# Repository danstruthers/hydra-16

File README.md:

## **Hydra 16**

A multitasking 65C02 computer and its operating system, HydraOS.

The Hydra-16's hardware gives each of 16 tasks its own 32K of RAM, zero page and stack included, with its own RAM and ROM bank selections, so a task switch is one register write.  HydraOS runs on it, Plan 9's way:
* **One kernel** in the BIOS ROM: a preemptive scheduler, one interrupt path, notes, memory and banks, and a jump table made from a specification.  Everything else is a module of the paged ROM, run in place in a task of its own.
* **A base to build on:** the kernel, a serial console driver, the kernel's devices and Woz's monitor are the base (`base/`), which HydraOS is built on and which boots on its own: [write an OS of your own](docs/09-programming/your-own-os.md) on it.
* **Everything a file:** devices are file servers (the console's windows, the disks and HydraFS, sound, GPIO and I2C, the clock, the Vera X, and `/pc`, a folder on the PC over the serial line), and each task has a namespace of its own, built by binds and mounts.
* **Shells and languages:** rc, Plan 9's shell, and the core tools; HyForth (Forth 2012), the login shell; hylang (danlang, a lisp); HyBASIC (QuickBASIC's kind, every number exact); SDKs for C (cc65) and assembly, and `as`, an assembler on the Hydra itself.
* **Tools:** a screen editor (`edit`), a debugger (`db`), a song player that plays ZSM songs and compiles scores as it plays.

The code is built with **cc65** (https://cc65.github.io/), and the board is designed in **KiCad 9** (https://www.kicad.org).

### **Quick start**

```
cd base
node build.js                      the base alone: the kernel, ser, kdev, the monitor (bin/bios_*.bin, bin/prom0.bin)
node sim/run.js -i                 its monitor in your terminal (Ctrl-A x quits)

cd ../reborn
node build.js                      build HydraOS (needs Node.js and cc65): bin/bios_*.bin, bin/prom0.bin ...
node sim/run.js -i                 use the Hydra in your terminal, in the emulator (Ctrl-A x quits)
node sim/web.js                    the emulator in a browser: one file, bin/hydra-16.html, to open (in Git: no
                                   Node.js needed to use it)
node sim/test.js                   the regression tests
```

The ROM images are in Git (`reborn/bin/`) and on each GitHub release, so the chips can be programmed without a toolchain.

### **Documentation**

**[The Hydra-16 book](docs/README.md)** is everything, in order: what the machine is, the board and how to build it
(the parts, the layout, the quirks), the kernel and its calls, the drivers, the shell, the languages, the tools, the
emulator, and the programming guide.  It's also [one PDF](docs/hydra-16.pdf), to print.

| Chapter | |
| :------ | :- |
| [1. The Hydra-16 at a glance](docs/01-overview.md) | The ideas, the software in layers, and a first hour in the emulator |
| [2. The hardware](docs/02-hardware/README.md) | The architecture, the devices, the parts, building it, the layout, the quirks, the cards |
| [3. The base](docs/03-base/README.md) | The boot, the kernel, files and namespaces, the system calls, the monitor |
| [4. The drivers](docs/04-drivers/README.md) | The serial console, the kernel's devices, storage, sound, GPIO, video |
| [5. The shell: rc](docs/05-rc.md) | Plan 9's shell |
| [6. The languages](docs/06-languages/README.md) | HyForth, hylang, HyBASIC, and the numbers they share |
| [7. The tools](docs/07-tools.md) | The core tools, the editors, the debugger, the assembler and disassembler |
| [8. The emulator](docs/08-emulator.md) | The emulator, the build, the tests, the PC tools |
| [9. The programming guide](docs/09-programming/README.md) | Assembly, C, servers and drivers, libraries, your own OS, every system call |

How it was designed, and where it stands: [the plan and the design notes](docs/design/README.md).

### **Repository**

| Folder | What |
| :----- | :--- |
| `base/` | The base: the kernel (the BIOS ROM), the system calls' specification, the console driver `ser`, the kernel's devices `kdev`, the monitor `wozmon`, the assembly SDK's core, the board's emulator and the tests' runner |
| `reborn/` | HydraOS, on the base: its modules, the SDKs, the ROM disk, the SD card's image, its tests |
| `docs/` | The book (its chapters, `docs/build`: the tools that make its parts list, layout drawings, call reference and PDF), and the design notes (`docs/design`) |
| `board/` | KiCad schematics and PCBs: the main board, the memory daughter card, the bus breakout card, the Vera X's glue board |
| `old/` | The old system (the 1.8C line: `os_rom/`, its programs, emulator, build and documents), frozen at HydraOS 1.0; `node old/build.js test` still builds and tests it |

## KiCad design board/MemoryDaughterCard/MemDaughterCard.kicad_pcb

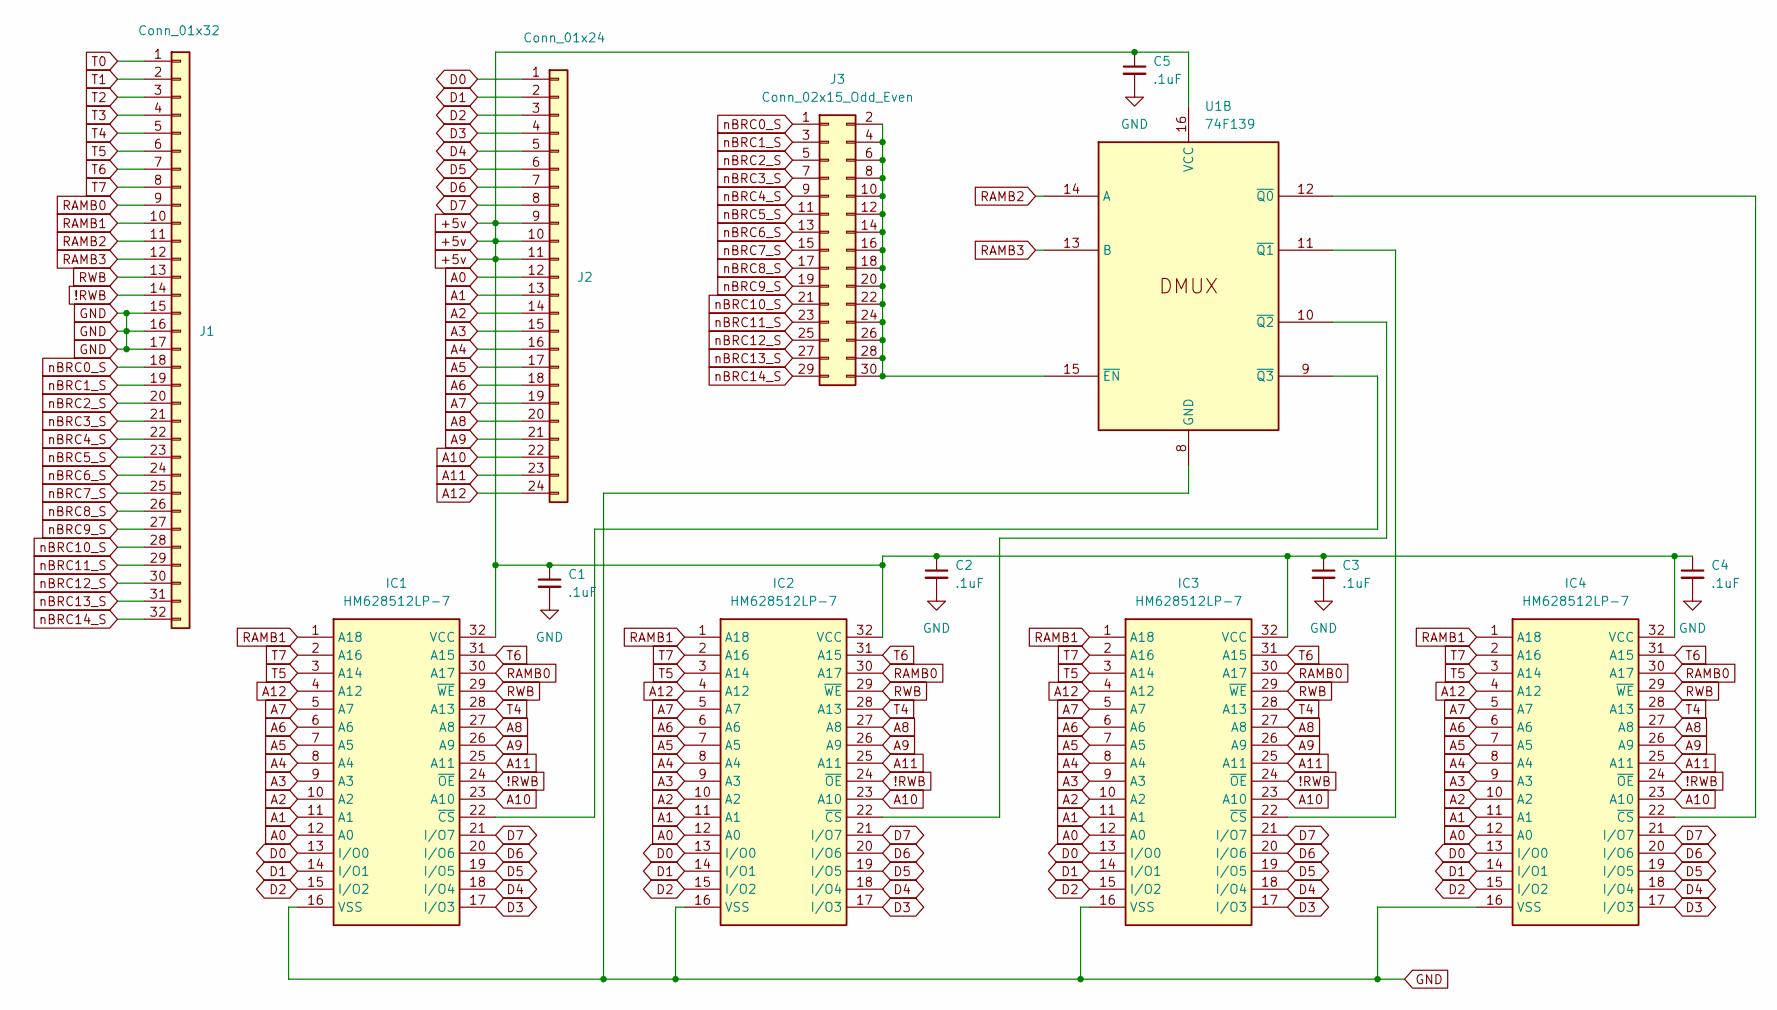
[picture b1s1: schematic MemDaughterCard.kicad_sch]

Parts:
C1, C2, C3, C4, C5: .1uF; C_Disc_D5.0mm_W2.5mm_P5.00mm
IC1, IC2, IC3, IC4: HM628512LP-7; DIP-32_W15.24mm_Socket_LongPads; Manufacturer_Part_Number HM628512LFP-7
J1: Conn_01x32; PinHeader_1x32_P2.54mm_Vertical
J2: Conn_01x24; PinHeader_1x24_P2.54mm_Vertical
J3: Conn_02x15_Odd_Even; PinHeader_2x15_P2.54mm_Vertical
U1: 74F139; DIP-16_W7.62mm

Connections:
!RWB: IC1.24 (~OE), IC2.24 (~OE), IC3.24 (~OE), IC4.24 (~OE), J1.14
+5v: C1.1, C2.1, C3.1, C4.1, C5.1, IC1.32 (VCC), IC2.32 (VCC), IC3.32 (VCC), IC4.32 (VCC), J2.9, J2.10, J2.11, U1.16 (VCC)
A0: IC1.12 (A0), IC2.12 (A0), IC3.12 (A0), IC4.12 (A0), J2.12
A1: IC1.11 (A1), IC2.11 (A1), IC3.11 (A1), IC4.11 (A1), J2.13
A2: IC1.10 (A2), IC2.10 (A2), IC3.10 (A2), IC4.10 (A2), J2.14
A3: IC1.9 (A3), IC2.9 (A3), IC3.9 (A3), IC4.9 (A3), J2.15
A4: IC1.8 (A4), IC2.8 (A4), IC3.8 (A4), IC4.8 (A4), J2.16
A5: IC1.7 (A5), IC2.7 (A5), IC3.7 (A5), IC4.7 (A5), J2.17
A6: IC1.6 (A6), IC2.6 (A6), IC3.6 (A6), IC4.6 (A6), J2.18
A7: IC1.5 (A7), IC2.5 (A7), IC3.5 (A7), IC4.5 (A7), J2.19
A8: IC1.27 (A8), IC2.27 (A8), IC3.27 (A8), IC4.27 (A8), J2.20
A9: IC1.26 (A9), IC2.26 (A9), IC3.26 (A9), IC4.26 (A9), J2.21
A10: IC1.23 (A10), IC2.23 (A10), IC3.23 (A10), IC4.23 (A10), J2.22
A11: IC1.25 (A11), IC2.25 (A11), IC3.25 (A11), IC4.25 (A11), J2.23
A12: IC1.4 (A12), IC2.4 (A12), IC3.4 (A12), IC4.4 (A12), J2.24
D0: IC1.13 (I/O0), IC2.13 (I/O0), IC3.13 (I/O0), IC4.13 (I/O0), J2.1
D1: IC1.14 (I/O1), IC2.14 (I/O1), IC3.14 (I/O1), IC4.14 (I/O1), J2.2
D2: IC1.15 (I/O2), IC2.15 (I/O2), IC3.15 (I/O2), IC4.15 (I/O2), J2.3
D3: IC1.17 (I/O3), IC2.17 (I/O3), IC3.17 (I/O3), IC4.17 (I/O3), J2.4
D4: IC1.18 (I/O4), IC2.18 (I/O4), IC3.18 (I/O4), IC4.18 (I/O4), J2.5
D5: IC1.19 (I/O5), IC2.19 (I/O5), IC3.19 (I/O5), IC4.19 (I/O5), J2.6
D6: IC1.20 (I/O6), IC2.20 (I/O6), IC3.20 (I/O6), IC4.20 (I/O6), J2.7
D7: IC1.21 (I/O7), IC2.21 (I/O7), IC3.21 (I/O7), IC4.21 (I/O7), J2.8
GND: C1.2, C2.2, C3.2, C4.2, C5.2, IC1.16 (VSS), IC2.16 (VSS), IC3.16 (VSS), IC4.16 (VSS), J1.15, J1.16, J1.17, U1.8 (GND)
unnamed: IC1.22 (~CS), U1.9 (~Q3)
unnamed: IC2.22 (~CS), U1.10 (~Q2)
unnamed: IC3.22 (~CS), U1.11 (~Q1)
unnamed: IC4.22 (~CS), U1.12 (~Q0)
unnamed: J3.2, J3.4, J3.6, J3.8, J3.10, J3.12, J3.14, J3.16, J3.18, J3.20, J3.22, J3.24, J3.26, J3.28, J3.30, U1.15 (~EN)
RAMB0: IC1.30 (A17), IC2.30 (A17), IC3.30 (A17), IC4.30 (A17), J1.9
RAMB1: IC1.1 (A18), IC2.1 (A18), IC3.1 (A18), IC4.1 (A18), J1.10
RAMB2: J1.11, U1.14 (A)
RAMB3: J1.12, U1.13 (B)
RWB: IC1.29 (~WE), IC2.29 (~WE), IC3.29 (~WE), IC4.29 (~WE), J1.13
T0: J1.1
T1: J1.2
T2: J1.3
T3: J1.4
T4: IC1.28 (A13), IC2.28 (A13), IC3.28 (A13), IC4.28 (A13), J1.5
T5: IC1.3 (A14), IC2.3 (A14), IC3.3 (A14), IC4.3 (A14), J1.6
T6: IC1.31 (A15), IC2.31 (A15), IC3.31 (A15), IC4.31 (A15), J1.7
T7: IC1.2 (A16), IC2.2 (A16), IC3.2 (A16), IC4.2 (A16), J1.8
nBRC0_S: J1.18, J3.1
nBRC1_S: J1.19, J3.3
nBRC2_S: J1.20, J3.5
nBRC3_S: J1.21, J3.7
nBRC4_S: J1.22, J3.9
nBRC5_S: J1.23, J3.11
nBRC6_S: J1.24, J3.13
nBRC7_S: J1.25, J3.15
nBRC8_S: J1.26, J3.17
nBRC9_S: J1.27, J3.19
nBRC10_S: J1.28, J3.21
nBRC11_S: J1.29, J3.23
nBRC12_S: J1.30, J3.25
nBRC13_S: J1.31, J3.27
nBRC14_S: J1.32, J3.29

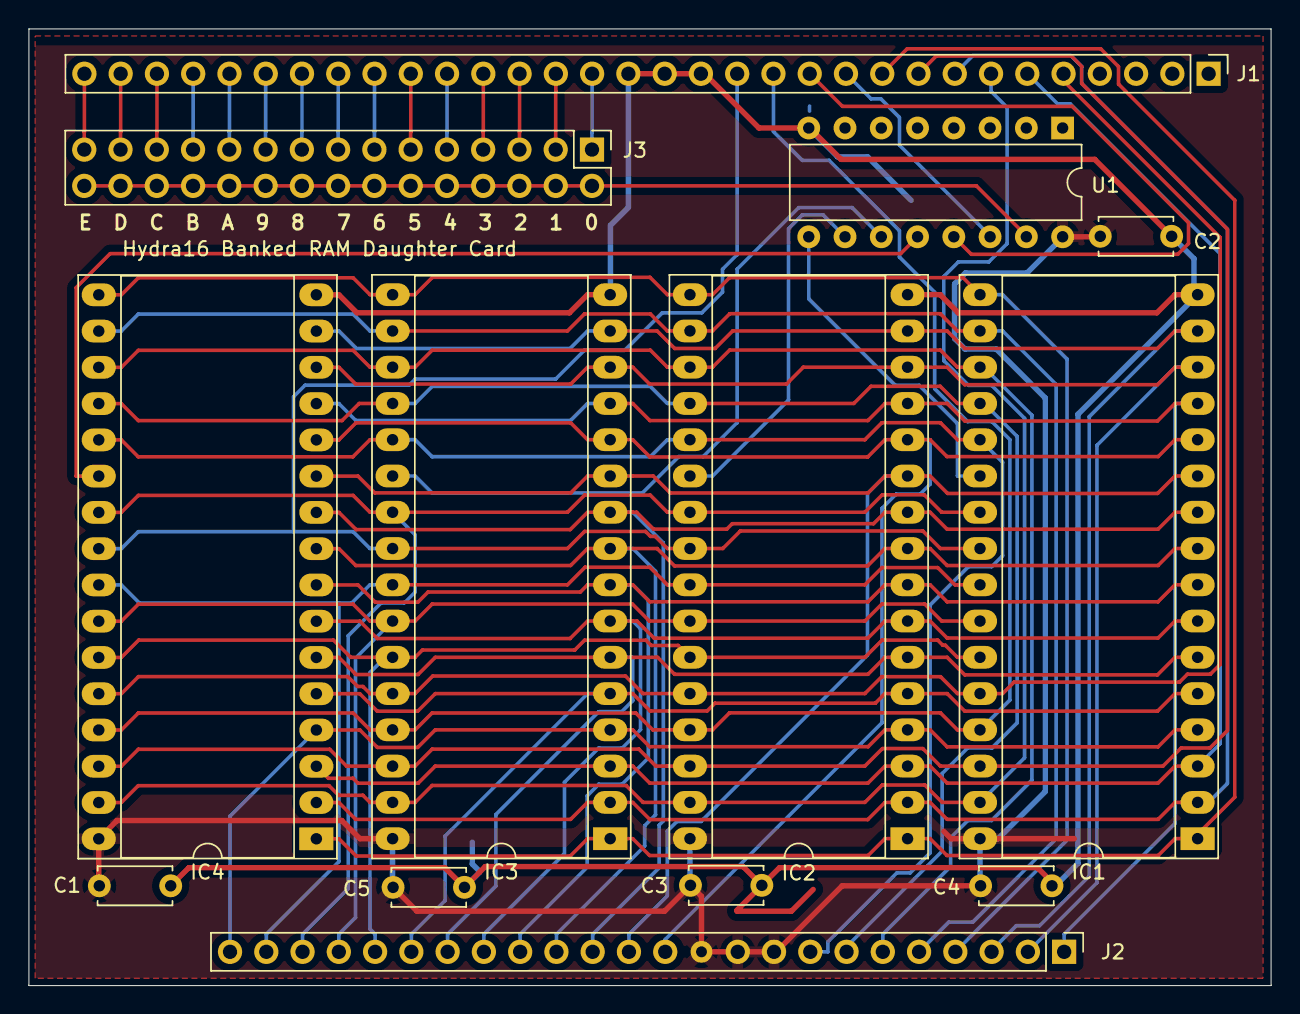
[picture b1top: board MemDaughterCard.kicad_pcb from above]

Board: 2 copper layers, 87.0 x 67.0 mm, 13 parts (0 on the bottom side), 53 nets.

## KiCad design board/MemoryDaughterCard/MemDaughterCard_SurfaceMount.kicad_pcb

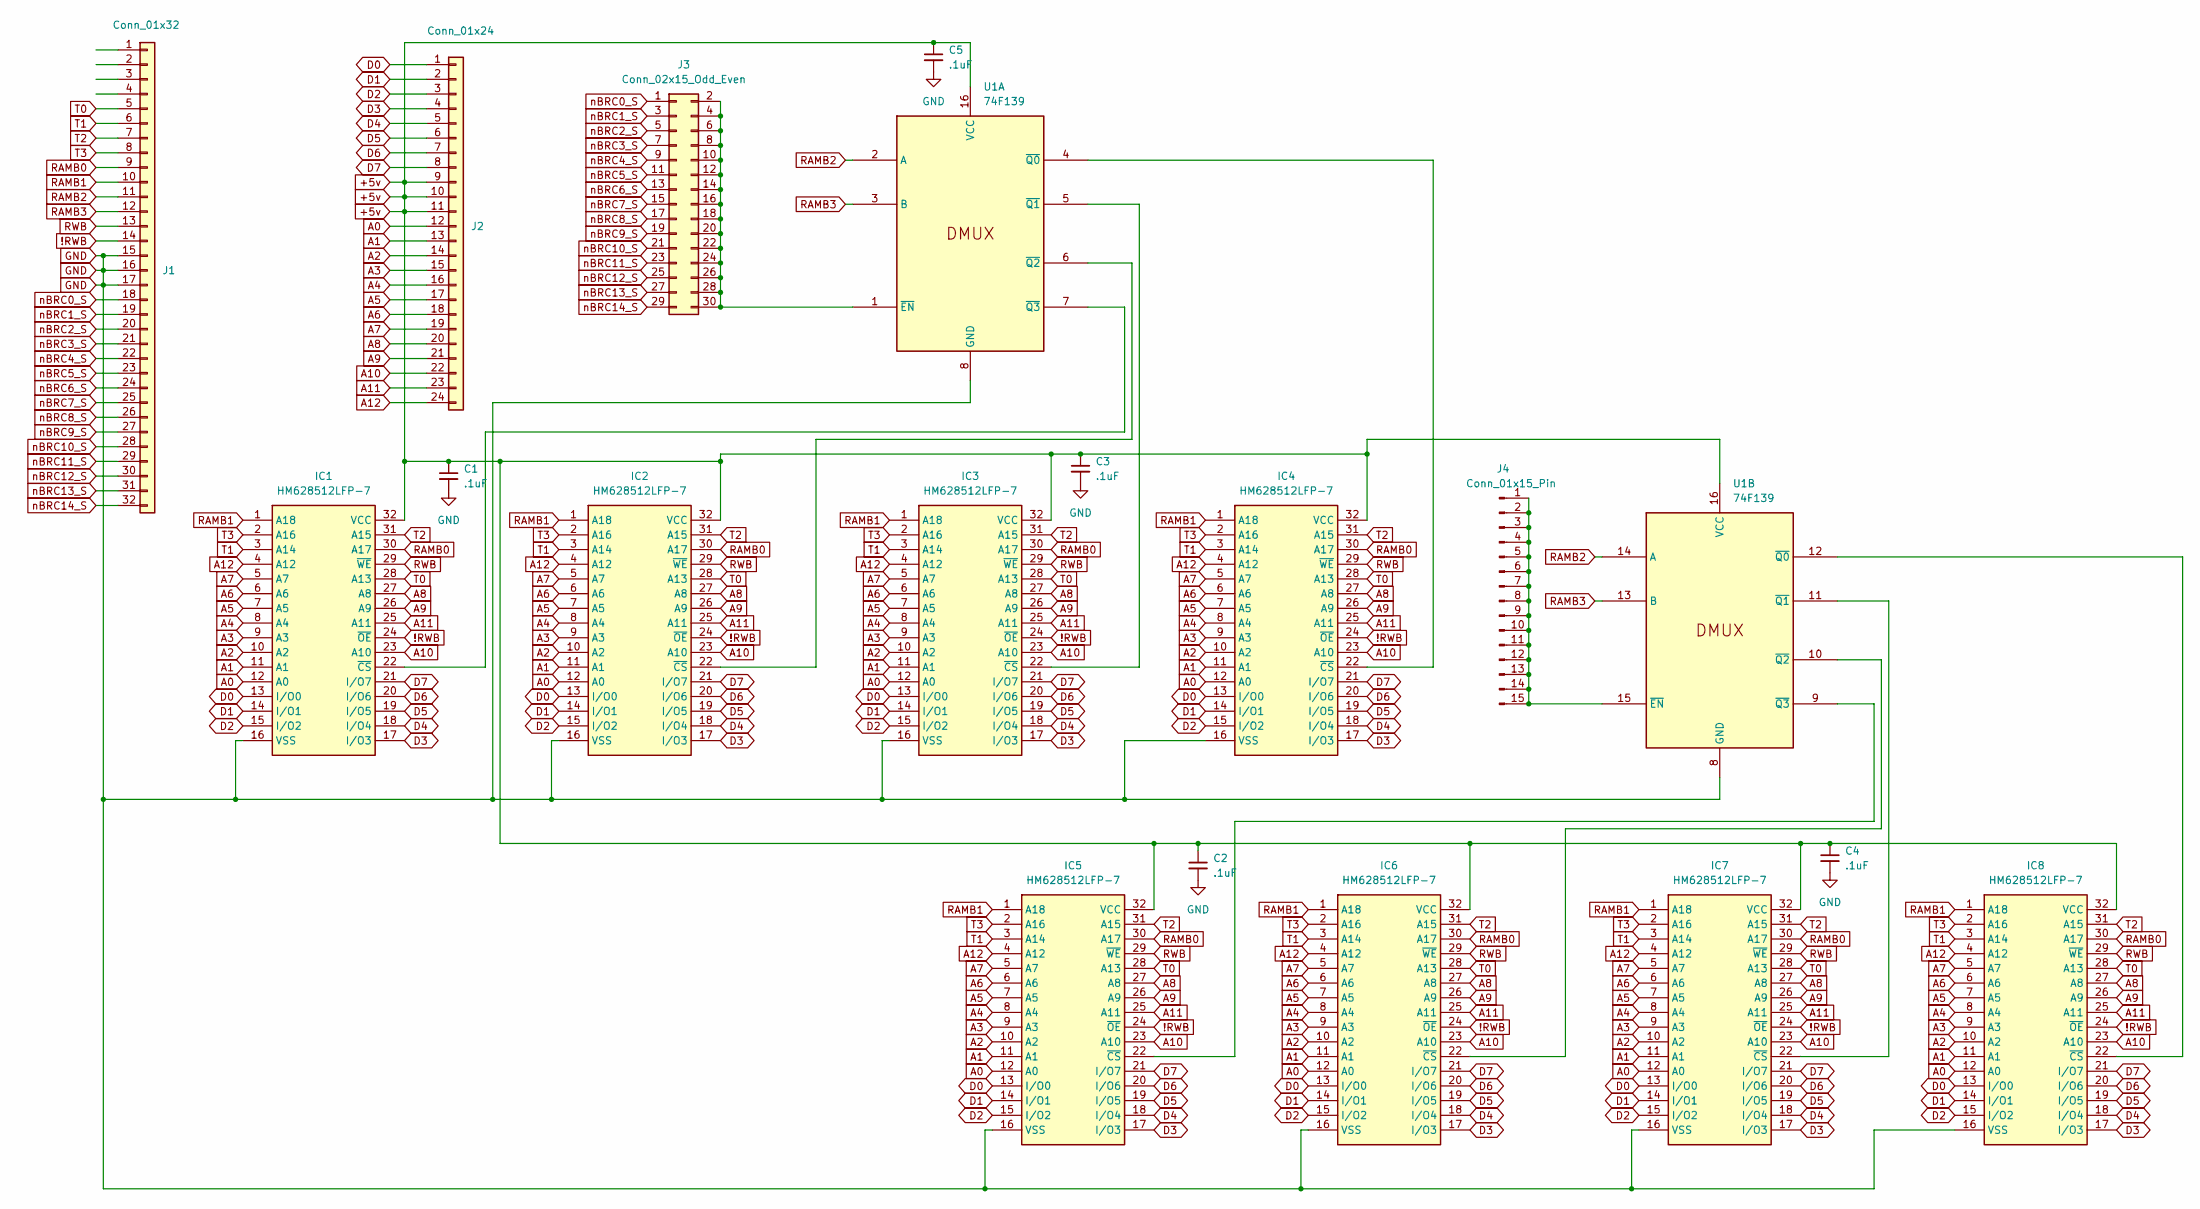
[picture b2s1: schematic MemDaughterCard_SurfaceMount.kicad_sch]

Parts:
C1, C2, C3, C4, C5: .1uF; C_Disc_D5.0mm_W2.5mm_P5.00mm
IC1, IC2, IC3, IC4, IC5, IC6, IC7, IC8: HM628512LFP-7; SOIC127P1414X300-32N; Manufacturer_Part_Number HM628512LFP-7
J1: Conn_01x32; PinHeader_1x32_P2.54mm_Vertical
J2: Conn_01x24; PinHeader_1x24_P2.54mm_Vertical
J3: Conn_02x15_Odd_Even; PinHeader_2x15_P2.54mm_Vertical
J4: Conn_01x15_Pin; PinHeader_1x15_P2.54mm_Vertical
U1: 74F139; DIP-16_W7.62mm

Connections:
!RWB: IC1.24 (~OE), IC2.24 (~OE), IC3.24 (~OE), IC4.24 (~OE), IC5.24 (~OE), IC6.24 (~OE), IC7.24 (~OE), IC8.24 (~OE), J1.14
+5v: C1.1, C2.1, C3.1, C4.1, C5.1, IC1.32 (VCC), IC2.32 (VCC), IC3.32 (VCC), IC4.32 (VCC), IC5.32 (VCC), IC6.32 (VCC), IC7.32 (VCC), IC8.32 (VCC), J2.9, J2.10, J2.11, U1.16 (VCC)
A0: IC1.12 (A0), IC2.12 (A0), IC3.12 (A0), IC4.12 (A0), IC5.12 (A0), IC6.12 (A0), IC7.12 (A0), IC8.12 (A0), J2.12
A1: IC1.11 (A1), IC2.11 (A1), IC3.11 (A1), IC4.11 (A1), IC5.11 (A1), IC6.11 (A1), IC7.11 (A1), IC8.11 (A1), J2.13
A2: IC1.10 (A2), IC2.10 (A2), IC3.10 (A2), IC4.10 (A2), IC5.10 (A2), IC6.10 (A2), IC7.10 (A2), IC8.10 (A2), J2.14
A3: IC1.9 (A3), IC2.9 (A3), IC3.9 (A3), IC4.9 (A3), IC5.9 (A3), IC6.9 (A3), IC7.9 (A3), IC8.9 (A3), J2.15
A4: IC1.8 (A4), IC2.8 (A4), IC3.8 (A4), IC4.8 (A4), IC5.8 (A4), IC6.8 (A4), IC7.8 (A4), IC8.8 (A4), J2.16
A5: IC1.7 (A5), IC2.7 (A5), IC3.7 (A5), IC4.7 (A5), IC5.7 (A5), IC6.7 (A5), IC7.7 (A5), IC8.7 (A5), J2.17
A6: IC1.6 (A6), IC2.6 (A6), IC3.6 (A6), IC4.6 (A6), IC5.6 (A6), IC6.6 (A6), IC7.6 (A6), IC8.6 (A6), J2.18
A7: IC1.5 (A7), IC2.5 (A7), IC3.5 (A7), IC4.5 (A7), IC5.5 (A7), IC6.5 (A7), IC7.5 (A7), IC8.5 (A7), J2.19
A8: IC1.27 (A8), IC2.27 (A8), IC3.27 (A8), IC4.27 (A8), IC5.27 (A8), IC6.27 (A8), IC7.27 (A8), IC8.27 (A8), J2.20
A9: IC1.26 (A9), IC2.26 (A9), IC3.26 (A9), IC4.26 (A9), IC5.26 (A9), IC6.26 (A9), IC7.26 (A9), IC8.26 (A9), J2.21
A10: IC1.23 (A10), IC2.23 (A10), IC3.23 (A10), IC4.23 (A10), IC5.23 (A10), IC6.23 (A10), IC7.23 (A10), IC8.23 (A10), J2.22
A11: IC1.25 (A11), IC2.25 (A11), IC3.25 (A11), IC4.25 (A11), IC5.25 (A11), IC6.25 (A11), IC7.25 (A11), IC8.25 (A11), J2.23
A12: IC1.4 (A12), IC2.4 (A12), IC3.4 (A12), IC4.4 (A12), IC5.4 (A12), IC6.4 (A12), IC7.4 (A12), IC8.4 (A12), J2.24
D0: IC1.13 (I/O0), IC2.13 (I/O0), IC3.13 (I/O0), IC4.13 (I/O0), IC5.13 (I/O0), IC6.13 (I/O0), IC7.13 (I/O0), IC8.13 (I/O0), J2.1
D1: IC1.14 (I/O1), IC2.14 (I/O1), IC3.14 (I/O1), IC4.14 (I/O1), IC5.14 (I/O1), IC6.14 (I/O1), IC7.14 (I/O1), IC8.14 (I/O1), J2.2
D2: IC1.15 (I/O2), IC2.15 (I/O2), IC3.15 (I/O2), IC4.15 (I/O2), IC5.15 (I/O2), IC6.15 (I/O2), IC7.15 (I/O2), IC8.15 (I/O2), J2.3
D3: IC1.17 (I/O3), IC2.17 (I/O3), IC3.17 (I/O3), IC4.17 (I/O3), IC5.17 (I/O3), IC6.17 (I/O3), IC7.17 (I/O3), IC8.17 (I/O3), J2.4
D4: IC1.18 (I/O4), IC2.18 (I/O4), IC3.18 (I/O4), IC4.18 (I/O4), IC5.18 (I/O4), IC6.18 (I/O4), IC7.18 (I/O4), IC8.18 (I/O4), J2.5
D5: IC1.19 (I/O5), IC2.19 (I/O5), IC3.19 (I/O5), IC4.19 (I/O5), IC5.19 (I/O5), IC6.19 (I/O5), IC7.19 (I/O5), IC8.19 (I/O5), J2.6
D6: IC1.20 (I/O6), IC2.20 (I/O6), IC3.20 (I/O6), IC4.20 (I/O6), IC5.20 (I/O6), IC6.20 (I/O6), IC7.20 (I/O6), IC8.20 (I/O6), J2.7
D7: IC1.21 (I/O7), IC2.21 (I/O7), IC3.21 (I/O7), IC4.21 (I/O7), IC5.21 (I/O7), IC6.21 (I/O7), IC7.21 (I/O7), IC8.21 (I/O7), J2.8
GND: C1.2, C2.2, C3.2, C4.2, C5.2, IC1.16 (VSS), IC2.16 (VSS), IC3.16 (VSS), IC4.16 (VSS), IC5.16 (VSS), IC6.16 (VSS), IC7.16 (VSS), IC8.16 (VSS), J1.15, J1.16, J1.17, U1.8 (GND)
unnamed: IC1.22 (~CS), U1.7 (~Q3)
unnamed: IC2.22 (~CS), U1.6 (~Q2)
unnamed: IC3.22 (~CS), U1.5 (~Q1)
unnamed: IC4.22 (~CS), U1.4 (~Q0)
unnamed: IC5.22 (~CS), U1.9 (~Q3)
unnamed: IC6.22 (~CS), U1.10 (~Q2)
unnamed: IC7.22 (~CS), U1.11 (~Q1)
unnamed: IC8.22 (~CS), U1.12 (~Q0)
unnamed: J3.2, J3.4, J3.6, J3.8, J3.10, J3.12, J3.14, J3.16, J3.18, J3.20, J3.22, J3.24, J3.26, J3.28, J3.30, U1.1 (~EN)
unnamed: J4.1, J4.2, J4.3, J4.4, J4.5, J4.6, J4.7, J4.8, J4.9, J4.10, J4.11, J4.12, J4.13, J4.14, J4.15, U1.15 (~EN)
RAMB0: IC1.30 (A17), IC2.30 (A17), IC3.30 (A17), IC4.30 (A17), IC5.30 (A17), IC6.30 (A17), IC7.30 (A17), IC8.30 (A17), J1.9
RAMB1: IC1.1 (A18), IC2.1 (A18), IC3.1 (A18), IC4.1 (A18), IC5.1 (A18), IC6.1 (A18), IC7.1 (A18), IC8.1 (A18), J1.10
RAMB2: J1.11, U1.2 (A), U1.14 (A)
RAMB3: J1.12, U1.3 (B), U1.13 (B)
RWB: IC1.29 (~WE), IC2.29 (~WE), IC3.29 (~WE), IC4.29 (~WE), IC5.29 (~WE), IC6.29 (~WE), IC7.29 (~WE), IC8.29 (~WE), J1.13
T0: IC1.28 (A13), IC2.28 (A13), IC3.28 (A13), IC4.28 (A13), IC5.28 (A13), IC6.28 (A13), IC7.28 (A13), IC8.28 (A13), J1.5
T1: IC1.3 (A14), IC2.3 (A14), IC3.3 (A14), IC4.3 (A14), IC5.3 (A14), IC6.3 (A14), IC7.3 (A14), IC8.3 (A14), J1.6
T2: IC1.31 (A15), IC2.31 (A15), IC3.31 (A15), IC4.31 (A15), IC5.31 (A15), IC6.31 (A15), IC7.31 (A15), IC8.31 (A15), J1.7
T3: IC1.2 (A16), IC2.2 (A16), IC3.2 (A16), IC4.2 (A16), IC5.2 (A16), IC6.2 (A16), IC7.2 (A16), IC8.2 (A16), J1.8
nBRC0_S: J1.18, J3.1
nBRC1_S: J1.19, J3.3
nBRC2_S: J1.20, J3.5
nBRC3_S: J1.21, J3.7
nBRC4_S: J1.22, J3.9
nBRC5_S: J1.23, J3.11
nBRC6_S: J1.24, J3.13
nBRC7_S: J1.25, J3.15
nBRC8_S: J1.26, J3.17
nBRC9_S: J1.27, J3.19
nBRC10_S: J1.28, J3.21
nBRC11_S: J1.29, J3.23
nBRC12_S: J1.30, J3.25
nBRC13_S: J1.31, J3.27
nBRC14_S: J1.32, J3.29

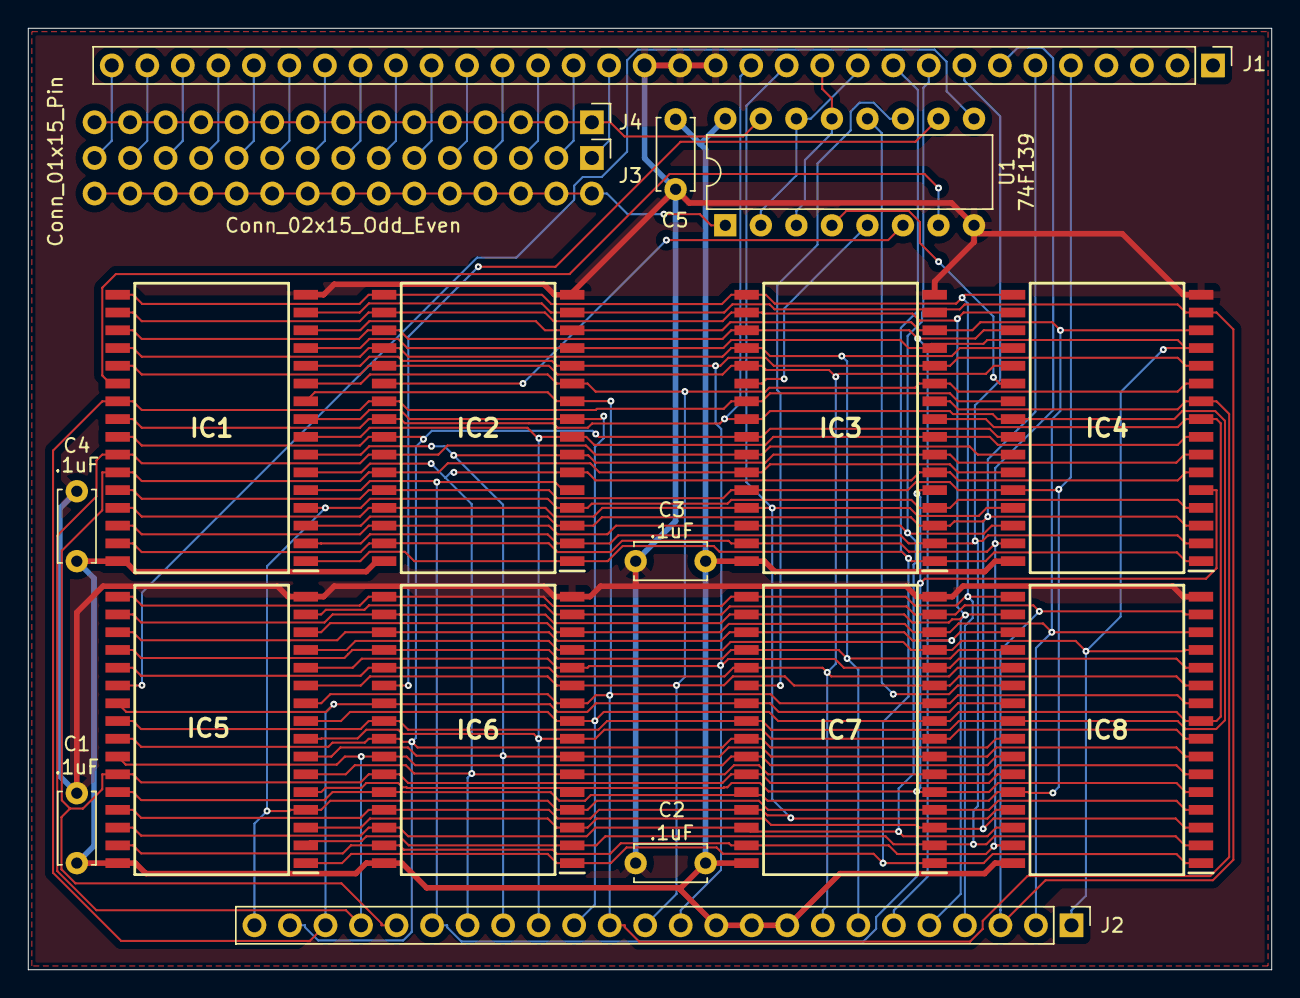
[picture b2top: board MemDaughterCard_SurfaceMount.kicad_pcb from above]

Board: 2 copper layers, 88.9 x 67.3 mm, 18 parts (0 on the bottom side), 58 nets.

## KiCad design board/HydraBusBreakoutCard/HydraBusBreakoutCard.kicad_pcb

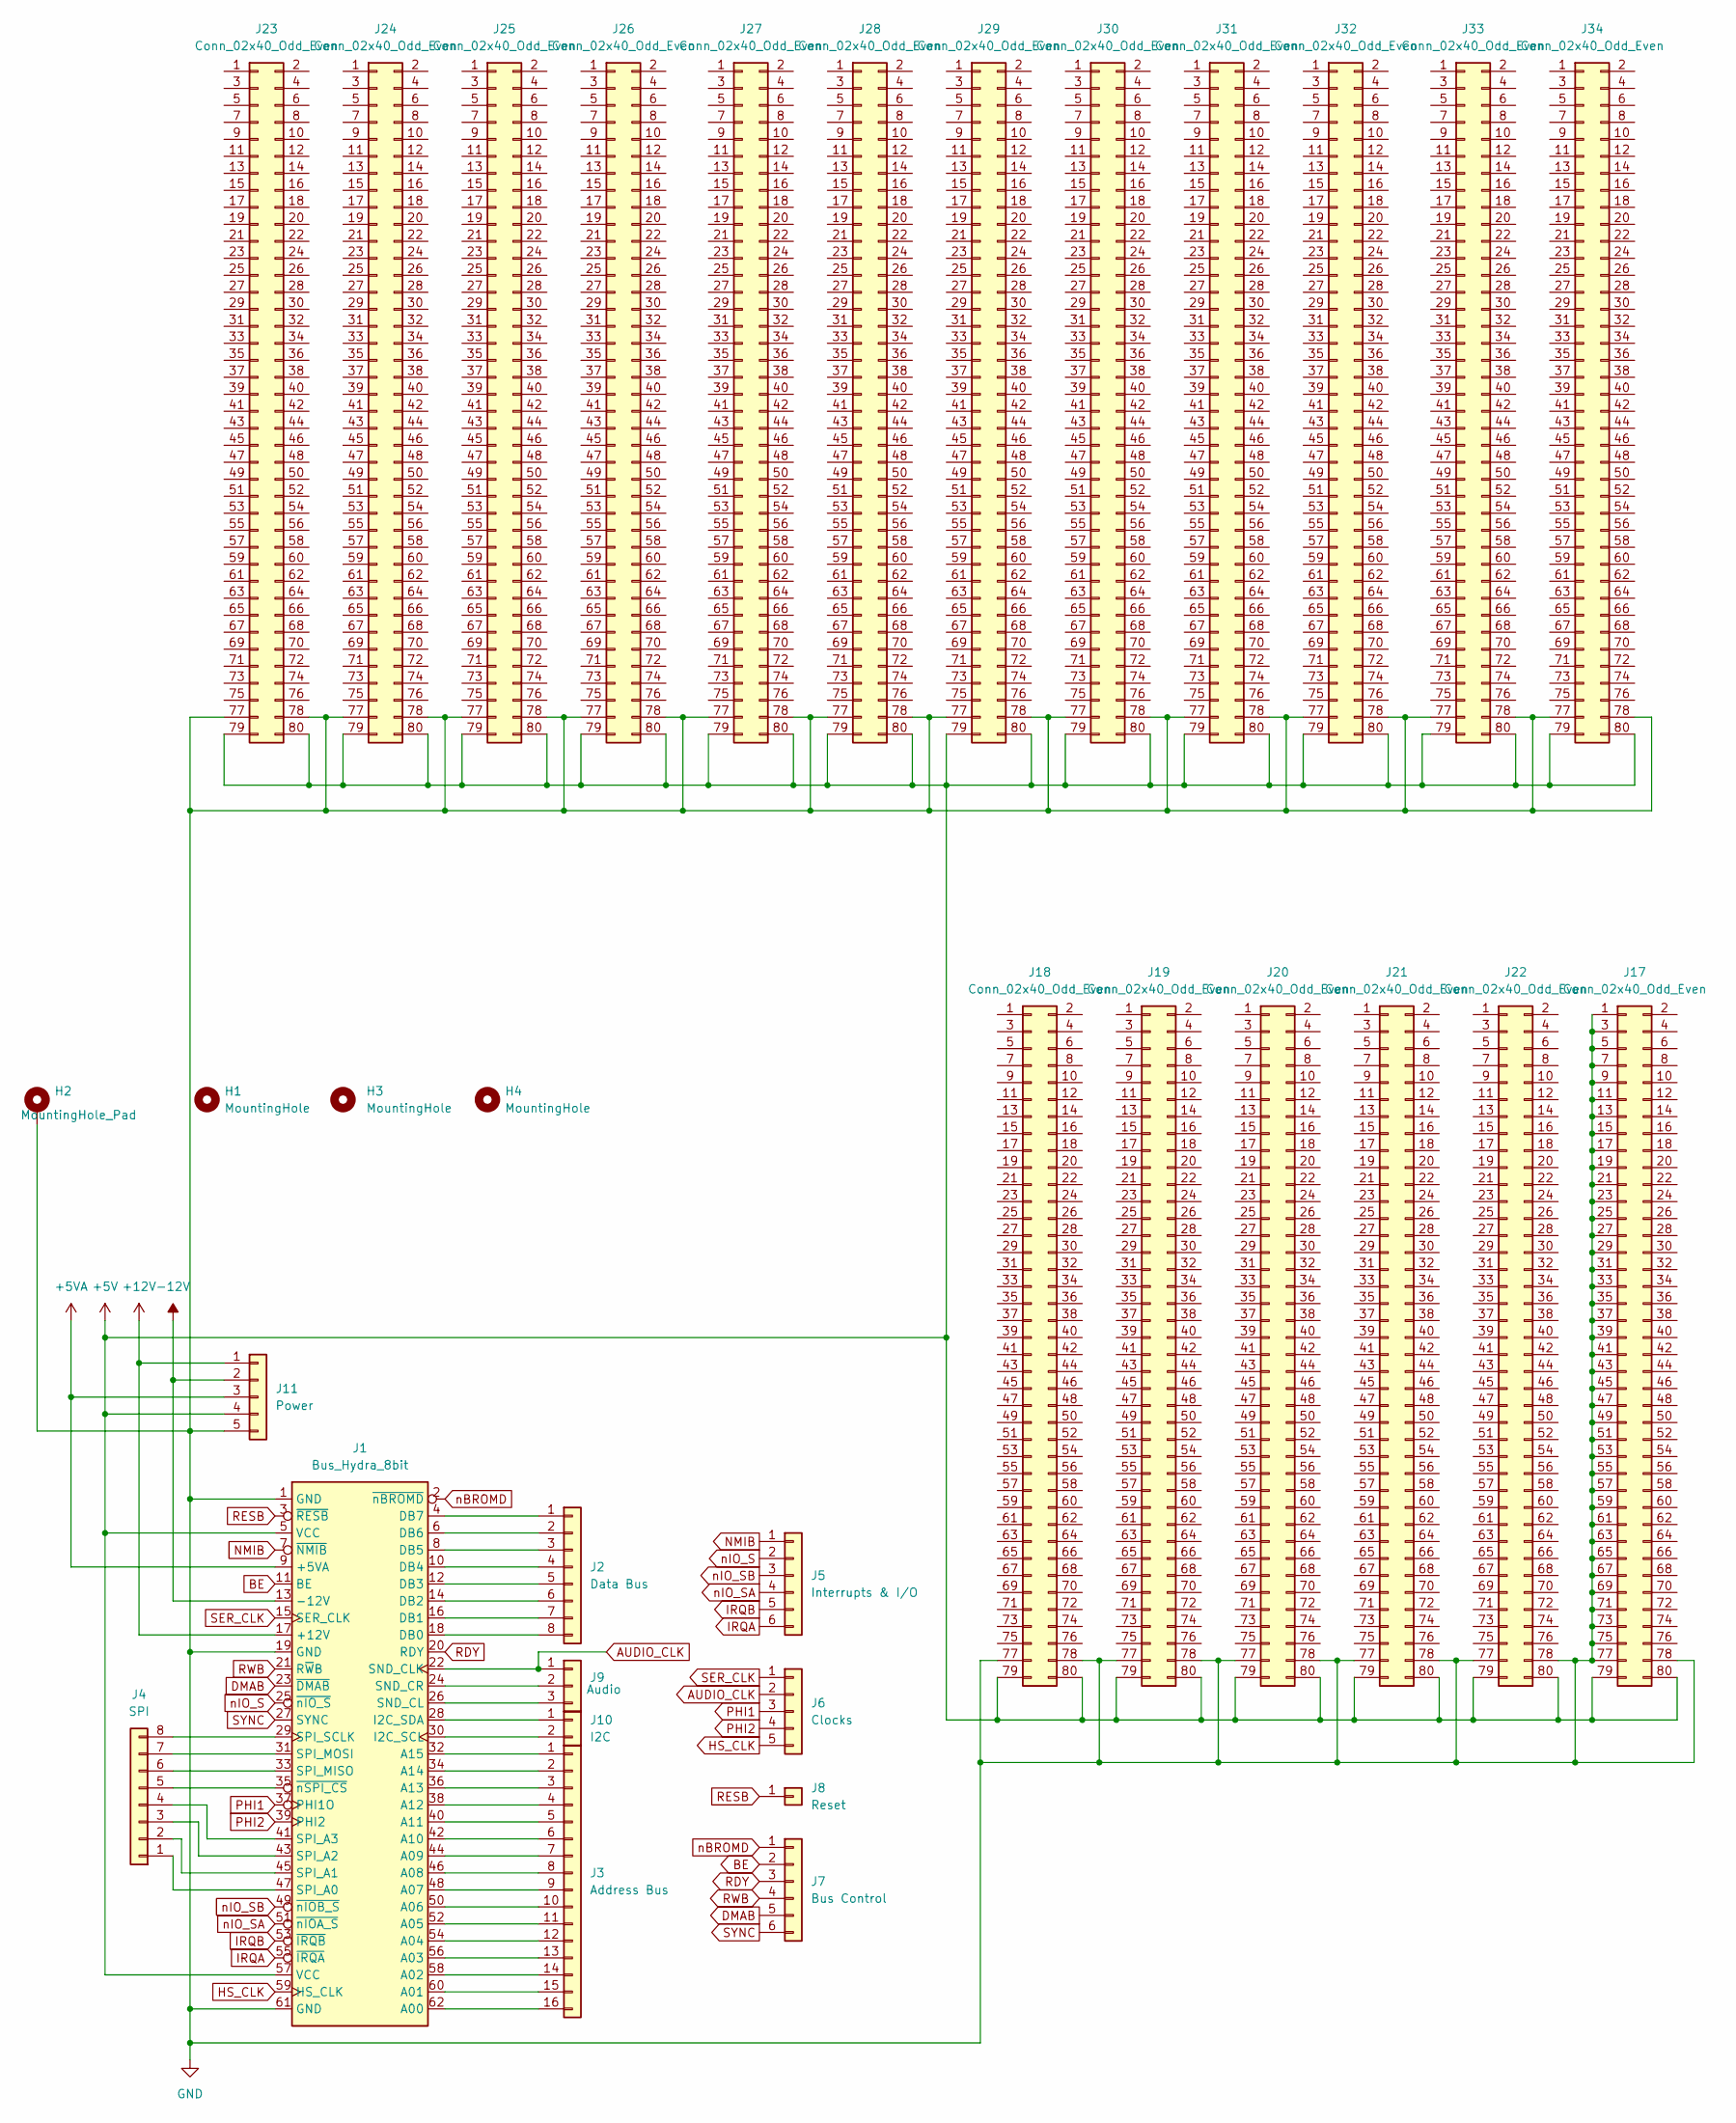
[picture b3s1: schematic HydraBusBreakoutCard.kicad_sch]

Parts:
H1, H3, H4: MountingHole; MountingHole_3.2mm_M3
H2: MountingHole_Pad; MountingHole_3.2mm_M3_ISO7380_Pad_TopBottom
J1: Bus_Hydra_8bit; BUS_Hydra_8Bit
J2: Data Bus; PinHeader_1x08_P2.54mm_Vertical
J3: Address Bus; PinHeader_1x16_P2.54mm_Vertical
J4: SPI; PinHeader_1x08_P2.54mm_Vertical
J5: Interrupts & I/O; PinHeader_1x06_P2.54mm_Vertical
J6: Clocks; PinHeader_1x05_P2.54mm_Vertical
J7: Bus Control; PinHeader_1x06_P2.54mm_Vertical
J8: Reset; PinHeader_1x01_P2.54mm_Vertical
J9: Audio; PinHeader_1x03_P2.54mm_Vertical
J10: I2C; PinHeader_1x02_P2.54mm_Vertical
J11: Power; PinHeader_1x05_P2.54mm_Vertical
J17, J18, J19, J20, J21, J22, J23, J24, J25, J26, J27, J28, J29, J30, J31, J32, J33, J34: Conn_02x40_Odd_Even; PinHeader_2x40_P2.54mm_Vertical

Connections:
+5V: J1.5 (VCC), J1.57 (VCC), J11.4, J17.79, J17.80, J18.79, J18.80, J19.79, J19.80, J20.79, J20.80, J21.79, J21.80, J22.79, J22.80, J23.79, J23.80, J24.79, J24.80, J25.79, J25.80, J26.79, J26.80, J27.79, J27.80, J28.79, J28.80, J29.79, J29.80, J30.79, J30.80, J31.79, J31.80, J32.79, J32.80, J33.79, J33.80, J34.79, J34.80
+5VA: J1.9 (+5VA), J11.3
+12V: J1.17 (+12V), J11.1
-12V: J1.13 (-12V), J11.2
AUDIO_CLK: J1.22 (SND_CLK), J6.2, J9.1
BE: J1.11 (BE), J7.2
DMAB: J1.23 (~DMAB), J7.5
GND: H2.1, J1.1 (GND), J1.19 (GND), J1.61 (GND), J11.5, J17.1, J17.3, J17.5, J17.7, J17.9, J17.11, J17.13, J17.15, J17.17, J17.19, J17.21, J17.23, J17.25, J17.27, J17.29, J17.31, J17.33, J17.35, J17.37, J17.39, J17.41, J17.43, J17.45, J17.47, J17.49, J17.51, J17.53, J17.55, J17.57, J17.59, J17.61, J17.63, J17.65, J17.67, J17.69, J17.71, J17.73, J17.75, J17.77, J17.78, J18.77, J18.78, J19.77, J19.78, J20.77, J20.78, J21.77, J21.78, J22.77, J22.78, J23.77, J23.78, J24.77, J24.78, J25.77, J25.78, J26.77, J26.78, J27.77, J27.78, J28.77, J28.78, J29.77, J29.78, J30.77, J30.78, J31.77, J31.78, J32.77, J32.78, J33.77, J33.78, J34.77, J34.78
HS_CLK: J1.59 (HS_CLK), J6.5
IRQA: J1.55 (~IRQA), J5.6
IRQB: J1.53 (~IRQB), J5.5
NMIB: J1.7 (~NMIB), J5.1
unnamed: J1.62 (A00), J3.16
unnamed: J1.60 (A01), J3.15
unnamed: J1.58 (A02), J3.14
unnamed: J1.56 (A03), J3.13
unnamed: J1.54 (A04), J3.12
unnamed: J1.52 (A05), J3.11
unnamed: J1.50 (A06), J3.10
unnamed: J1.48 (A07), J3.9
unnamed: J1.46 (A08), J3.8
unnamed: J1.44 (A09), J3.7
unnamed: J1.42 (A10), J3.6
unnamed: J1.40 (A11), J3.5
unnamed: J1.38 (A12), J3.4
unnamed: J1.36 (A13), J3.3
unnamed: J1.34 (A14), J3.2
unnamed: J1.32 (A15), J3.1
unnamed: J1.18 (DB0), J2.8
unnamed: J1.16 (DB1), J2.7
unnamed: J1.14 (DB2), J2.6
unnamed: J1.12 (DB3), J2.5
unnamed: J1.10 (DB4), J2.4
unnamed: J1.8 (DB5), J2.3
unnamed: J1.6 (DB6), J2.2
unnamed: J1.4 (DB7), J2.1
unnamed: J1.30 (I2C_SCL), J10.2
unnamed: J1.28 (I2C_SDA), J10.1
unnamed: J1.26 (SND_CL), J9.3
unnamed: J1.24 (SND_CR), J9.2
unnamed: J1.47 (SPI_A0), J4.1
unnamed: J1.45 (SPI_A1), J4.2
unnamed: J1.43 (SPI_A2), J4.3
unnamed: J1.41 (SPI_A3), J4.4
unnamed: J1.33 (SPI_MISO), J4.6
unnamed: J1.31 (SPI_MOSI), J4.7
unnamed: J1.29 (SPI_SCLK), J4.8
unnamed: J1.35 (~nSPI_CS), J4.5
PHI1: J1.37 (PHI1O), J6.3
PHI2: J1.39 (PHI2), J6.4
RDY: J1.20 (RDY), J7.3
RESB: J1.3 (~RESB), J8.1
RWB: J1.21 (R~WB), J7.4
SER_CLK: J1.15 (SER_CLK), J6.1
SYNC: J1.27 (SYNC), J7.6
nBROMD: J1.2 (~nBROMD), J7.1
nIO_S: J1.25 (~nIO_S), J5.2
nIO_SA: J1.51 (~nIOA_S), J5.4
nIO_SB: J1.49 (~nIOB_S), J5.3

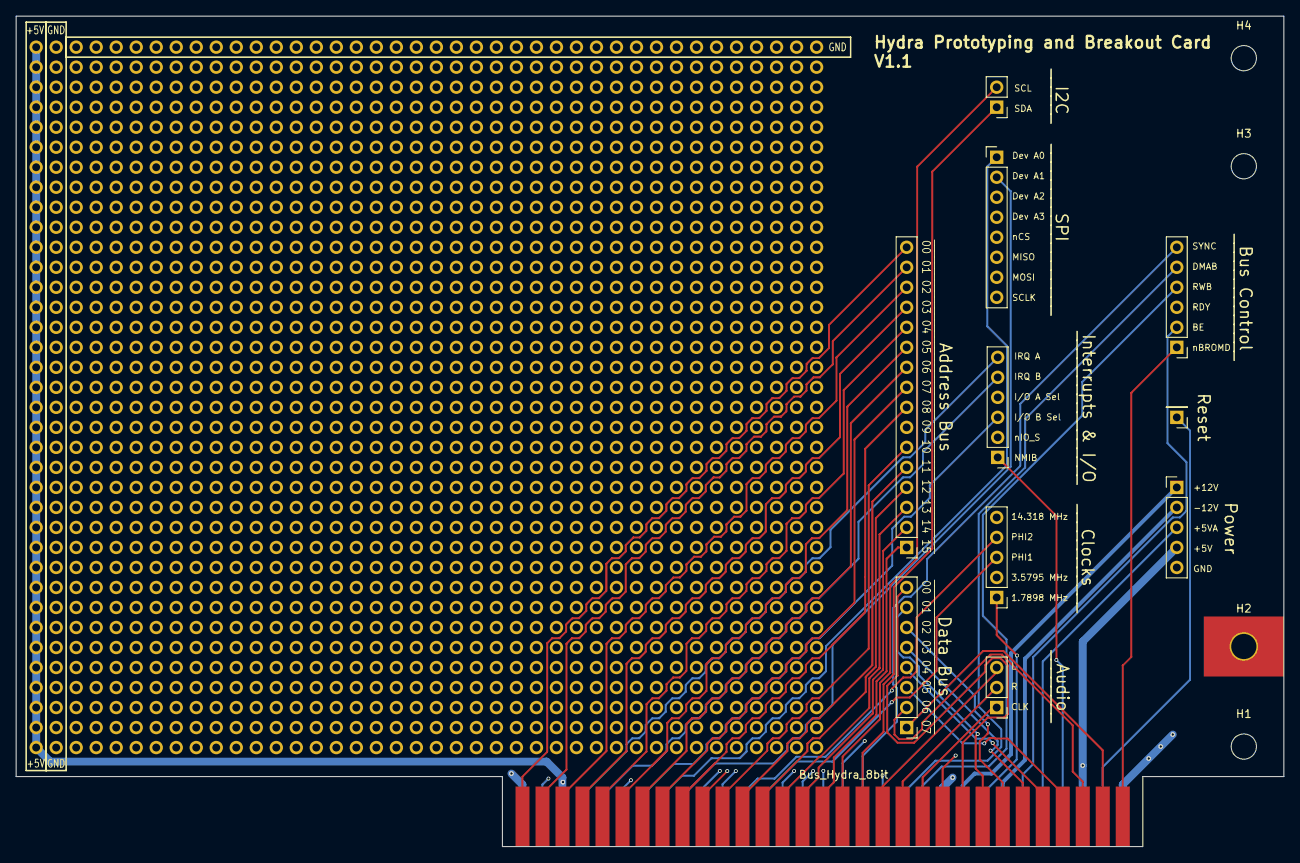
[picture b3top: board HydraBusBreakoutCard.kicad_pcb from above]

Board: 4 copper layers, 160.9 x 105.4 mm, 33 parts (0 on the bottom side), 59 nets.
